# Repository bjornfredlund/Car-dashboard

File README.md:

# Custom ESP32-Based PCB with Bluetooth & Sensor Integration

## Overview

Custom PCB built around the **ESP32** microcontroller. The board integrates multiple sensors and modules, making it suitable for applications such as **data logging, motion tracking, FM transmission, and GNSS-based navigation**. Sample project using the [board](https://github.com/bjornfredlund/ESP32-Car-Dashboard) as a Car dashboard/telemetry unit, providing positiong, velocity, acceleration and bluetooth transmitting capabilities.

## Features
- **ESP32-WROOM-E**
- **TMP117AIDRVR Temperature Sensor**
- **MicroSD Card Reader**
- **TCA9517DGKRQ1 Level shifter for 5v I2C communication** 
- **PCM5102 DAC for Audio Processing**
- **I2C bus to FM Radio Transmitter**
- **LIS2DH12TR Accelerometer**
- **GNSS Receiver via UART**
- **3 User-Programmable Buttons**
## Requirements

- **ESP-IDF v5.3** – Required for firmware development and deployment.

## Applications

- **Wireless Sensor Hub** – Collect and transmit sensor data over Bluetooth.
- **Portable FM Transmitter** – Stream audio to nearby FM receivers.
- **Data Logger** – Store sensor data on an SD card for later analysis.
- **Motion & Position Tracking** – Use accelerometer and GNSS for movement-based applications.

## Getting Started

### 1. **Hardware Setup**

- Power the PCB via **USB or an external battery**.
- Connect necessary peripherals (antennas, audio sources, etc.).

### 2. **Firmware Development**

- Use the **ESP-IDF** or **Arduino IDE** to program the ESP32.
- Implement communication with the sensors and peripherals via **I2C, UART, and SPI**.

### 3. I2C Device addresses 
    TMP117AIDRVR: 0x48
    PCM5102: 0xC0
    LIS2DH12TR: 0x19

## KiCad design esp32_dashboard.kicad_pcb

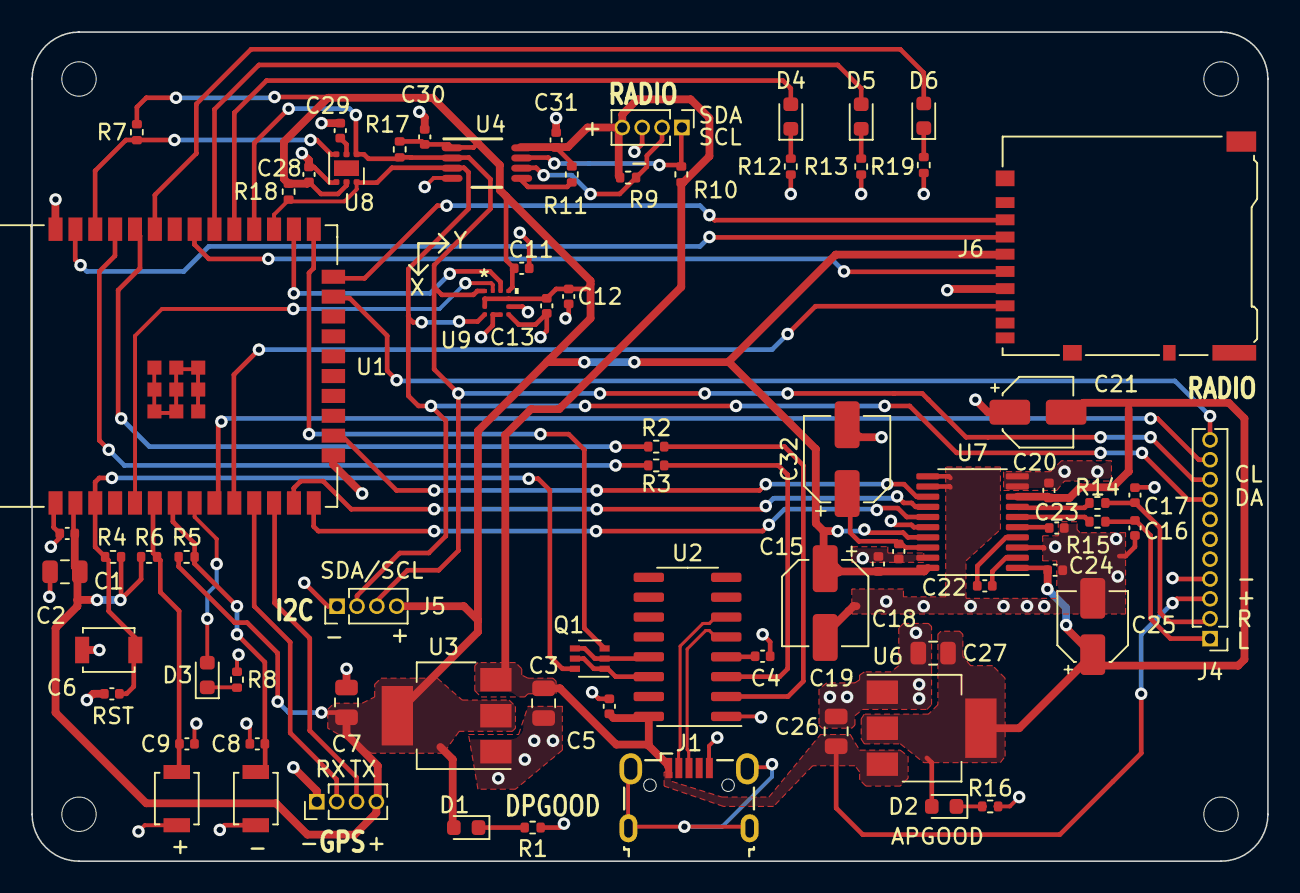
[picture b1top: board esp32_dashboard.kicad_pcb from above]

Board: 2 copper layers, 79.0 x 53.0 mm, 77 parts (0 on the bottom side), 55 nets.

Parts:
C1, C3, C7, C26, C27: 22uF; C_0805_2012Metric
C2, C8, C9, C15, C18, C20, C24: 0.1uF; C_0402_1005Metric
C4, C5, C6, C11, C13, C28, C29, C30, C31: 100nF; C_0402_1005Metric
C12: 10uF; C_0402_1005Metric
C16, C17: 2.2nF; C_0402_1005Metric
C19, C32: 10uF; CP_Elec_5x5.3
C21, C25: 10uF; CP_Elec_4x3
C22, C23: 2.2uF; C_0402_1005Metric
D1, D2, D3, D4, D5, D6: RED; LED_0603_1608Metric
H1, H2, H3, H4: MountingHole; MountingHole_2.2mm_M2
J1: USB_B_Micro; USB_Micro-B_Wuerth_629105150521
J2, J3, J5: Conn_01x04_Pin; PinHeader_1x04_P1.27mm_Vertical
J4: Conn_01x11_Pin; PinHeader_1x11_P1.27mm_Vertical
J6: Micro_SD_Card; microSD_HC_Hirose_DM3AT-SF-PEJM5
Q1: UMH3N; SOT-363_SC-70-6
R1, R8, R12, R13, R16, R19: 1k; R_0402_1005Metric
R2, R3: 0; R_0402_1005Metric
R4, R11: 10k; R_0402_1005Metric
R5, R6: 1K; R_0402_1005Metric
R7, R9, R10, R17, R18: 4k7; R_0402_1005Metric
R14, R15: 470; R_0402_1005Metric
SW1, SW2, SW3: SW_Push; SW_SPST_B3U-1000P
U1: ESP32-WROOM-E; ESP32-WROOM-32E
U2: CH340C; SOIC-16_3.9x9.9mm_P1.27mm
U3, U6: AMS1117-3.3; SOT-223-3_TabPin2
U4: TCA9517DGKRQ1; DGK0008A_N
U7: PCM5102A; TSSOP-20_4.4x6.5mm_P0.65mm
U8: TMP117xxDRV; WSON-6-1EP_2x2mm_P0.65mm_EP1x1.6mm
U9: LIS2DH12TR; LGA-12_STM

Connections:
5V: C3.1, C5.1, C26.1, C31.2, J1.1 (VBUS), J2.4, J4.3, R9.1, R10.1, R11.2, U2.16 (VCC), U3.3 (VI), U4.8 (VCCB), U6.3 (VI)
+3V3: C1.1, C2.1, C7.2, C11.1, C12.1, C13.1, C15.1, C19.1, C28.1, C30.1, D1.2 (A), J3.4, J5.4, J6.4 (VDD), R4.1, R5.1, R6.1, R7.1, R17.1, R18.1, U1.2 (3V3), U3.2 (VO), U4.1 (VCCA), U7.17 (XSMT), U7.20 (DVDD), U8.5 (V+), U9.2 (CS), U9.3 (SDO/SA0), U9.9 (VDD), U9.10 (VDD_IO)
/ACC_INT1: U1.5 (SENSOR_VN/GPIO39/ADC1_CH3), U9.12 (INT1)
/ACC_INT2: U1.26 (ADC2_CH0/GPIO4), U9.11 (INT2)
/Audio/Lout: C16.1, J4.1, R14.2
/Audio/Rout: C17.1, J4.2, R15.1
/BOOT: Q1.3 (C2), U1.25 (GPIO0/BOOT/ADC2_CH1)
/BTN1: C8.1, R5.2, SW1.1, U1.7 (GPIO35/ADC1_CH7)
/BTN2: C9.1, R6.2, SW3.1, U1.6 (GPIO34/ADC1_CH6)
/DTR: Q1.2 (B1), Q1.4 (E2), U2.13 (~DTR)
/EN: C6.1, Q1.6 (C1), R4.2, SW2.1, U1.3 (EN/CHIP_PU)
/RTS: Q1.1 (E1), Q1.5 (B2), U2.14 (~RTS)
/RXD0: R2.2, U1.34 (U0RXD/GPIO3)
/RX_GPS: J3.2, U1.11 (DAC_2/ADC2_CH9/GPIO26)
/SCL5v: J2.1, R10.2, U4.7 (SCLB)
/SDA5v: J2.2, R9.2, U4.6 (SDAB)
/TXD0: R3.2, U1.35 (U0TXD/GPIO1)
/TX_GPS: J3.3, U1.12 (ADC2_CH7/GPIO27)
/T_ALERT: R7.2, U1.36 (GPIO22), U8.3 (ALERT)
/USB+: J1.3 (D+), U2.5 (UD+)
/USB-: J1.2 (D-), U2.6 (UD-)
ESP_OK: D3.2 (A), U1.8 (32K_XP/GPIO32/ADC1_CH4)
GND: C1.2, C2.2, C3.2, C4.1, C5.2, C6.2, C7.1, C8.2, C9.2, C11.2, C12.2, C13.2, C15.2, C16.2, C17.2, C18.1, C19.2, C20.2, C21.1, C23.2, C24.1, C25.2, C26.2, C27.1, C28.2, C29.2, C30.2, C31.1, C32.2, J1.5 (GND), J2.3, J3.1, J4.4, J5.1, J6.6 (VSS), R1.2, R8.2, R12.2, R13.2, R16.2, R19.2, SW1.2, SW2.2, SW3.2, U1.1 (GND), U1.15 (GND), U1.38 (GND), U2.1 (GND), U3.1 (GND), U4.4 (GND), U6.1 (GND), U7.3 (CPGND), U7.9 (AGND), U7.10 (DEMP), U7.11 (FLT), U7.12 (SCK), U7.16 (FMT), U7.19 (DGND), U8.4 (ADD0), U9.5 (RES), U9.6 (GND), U9.7 (GND), U9.8 (GND)
I2S_BCK: U1.16 (MTCK/GPIO13/ADC2_CH4), U7.13 (BCK)
I2S_DATA: U1.13 (MTMS/GPIO14/ADC2_CH6), U7.14 (DIN)
I2S_LRCK: U1.14 (MTDI/GPIO12/ADC2_CH5), U7.15 (LRCK)
LED_0: D4.2 (A), U1.29 (GPIO5)
LED_1: D5.2 (A), U1.30 (GPIO18)
LED_2: D6.2 (A), U1.33 (GPIO21)
MISO: J6.7 (DAT0), U1.10 (DAC_1/ADC2_CH8/GPIO25)
MOSI: J6.3 (CMD), U1.37 (GPIO23)
unnamed: D1.1 (K), R1.1
unnamed: D2.1 (K), R16.1
unnamed: D3.1 (K), R8.1
unnamed: D4.1 (K), R12.1
unnamed: D5.1 (K), R13.1
unnamed: D6.1 (K), R19.1
unnamed: R3.1, U2.3 (RXD)
unnamed: R2.1, U2.2 (TXD)
unnamed: C4.2, U2.4 (V3)
unnamed: R11.1, U4.5 (EN)
unnamed: C22.2, U7.4 (CAPM)
unnamed: C22.1, U7.2 (CAPP)
unnamed: C18.2, C32.1, U7.18 (LDOO)
unnamed: R14.1, U7.6 (OUTL)
unnamed: R15.2, U7.7 (OUTR)
unnamed: C23.1, U7.5 (VNEG)
unnamed: C29.1, U8.2 (GND)
SCK: J6.5 (CLK), U1.31 (GPIO19)
SCL3v3: J4.9, J5.3, R17.2, U1.28 (GPIO17), U4.2 (SCLA), U8.1 (SCL), U9.1 (SCL/SPC)
SDA3v3: J4.8, J5.2, R18.2, U1.27 (GPIO16), U4.3 (SDAA), U8.6 (SDA), U9.4 (SDA/SDI/SDO)
Si Addr: J4.10, U1.9 (32K_XN/GPIO33/ADC1_CH5)
Si RST: J4.11, U1.23 (MTDO/GPIO15/ADC2_CH3)
VDDA: C20.1, C21.2, C24.2, C25.1, C27.2, D2.2 (A), U6.2 (VO), U7.1 (CPVDD), U7.8 (AVDD)
uSD_CS: J6.2 (DAT3/CD), U1.24 (ADC2_CH2/GPIO2)

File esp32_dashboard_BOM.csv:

"Id";"Designator";"Footprint";"Quantity";"Designation";"Manufacturer";"Mfg part";
1;"U9";"LGA-12_STM";1;"LIS2DH12TR";"STMicroelectronics";"LIS2DUX12TR";
2;"C13,C11,C30,C29,C5,C28,C4,C31,C6";"C_0402_1005Metric";9;"100nF";"Murata Electronics";"GMD155R71C104KA11D";
3;"C12";"C_0402_1005Metric";1;"10uF";"KYOCERA AVX";"CM05X5R106M10AH";
4;"C21,C25";"CP_Elec_4x3";2;"10uF";"Wurth Elektronik";"865060643005";
5;"J2,J5,J3";"PinHeader_1x04_P1.27mm_Vertical";3;"Conn_01x04_Pin";"SAMTEC";"SAM1029-04-ND";
6;"D1,D5,D2,D6,D4,D3";"LED_0603_1608Metric";6;"GREEN";"VISHAY";"TLMP1100-GS08";
7;"R10,R9,R7,R18,R17";"R_0402_1005Metric";5;"4k7";"YAGEO";"RC0402JR-074K7L";
8;"R2,R3";"R_0402_1005Metric";2;"0";"Panasonic Electronic Components";"ERJ-2GE0R00X";
9;"U4";"DGK0008A_N";1;"TCA9517DGKRQ1";"Texas Instruments";"TCA9517DGKRQ1";
10;"J4";"PinHeader_1x11_P1.27mm_Vertical";1;"Conn_01x11_Pin";"Adam Tech";"PH1-11-UA";
11;"C24,C20,C2,C15,C8,C9,C18";"C_0402_1005Metric";7;"0.1uF";"TAIYO YUDEN";"MBASU105SB7104KFNA01";
13;"C17,C16";"C_0402_1005Metric";2;"2.2nF";"KEMET";"C0402C222K5RACAUTO";
14;"R11,R4";"R_0402_1005Metric";2;"10k";"VISHAY";"CRCW040210K0FKED";
15;"J1";"USB_Micro-B_Wuerth_629105150521";1;"USB_B_Micro";"Wurth Elektronik";"629105150521";
16;"U7";"TSSOP-20_4.4x6.5mm_P0.65mm";1;"PCM5102A";"Texas Instruments";"PCM5102APWR";
17;"R12,R13,R8,R16,R19,R1";"R_0402_1005Metric";6;"1k";"VISHAY";"CRCW04021K00FKED";
18;"C32,C19";"CP_Elec_5x5.3";2;"10uF";"Nichicon";"UWT1E100MCL1GB";
20;"U8";"WSON-6-1EP_2x2mm_P0.65mm_EP1x1.6mm";1;"TMP117xxDRV";"Texas Instruments";"TMP117AIDRVR";
21;"C1,C7,C27,C3,C26";"C_0805_2012Metric";5;"22uF";"YAGEO";"CC0805MKX5R7BB226";
22;"SW3,SW1,SW2";"SW_SPST_B3U-1000P";3;"SW_Push";"Omron Electronics Inc-EMC Div";"B3U-1000P"
23;"Q1";"SOT-363_SC-70-6";1;"UMH3N";"Jiangsu Changjing Electronics Technology Co., Ltd.";"UMH3N";
24;"R14,R15";"R_0402_1005Metric";2;"470";"VISHAY";"CRCW0402470RFKED";
25;"R6,R5";"R_0402_1005Metric";2;"1K";"VISHAY";"CRCW04021K00FKED.";
26;"U1";"ESP32-WROOM-32E";1;"ESP32-WROOM-E";"Espressif Systems";"ESP32-WROOM-32E-N16";
27;"U2";"SOIC-16_3.9x9.9mm_P1.27mm";1;"CH340C";"WCH(Jiangsu Qin Heng)";"CH340C";
28;"J6";"microSD_HC_Hirose_DM3AT-SF-PEJM5";1;"Micro_SD_Card";"HIROSE;"DM3AT-SF-PEJM5";
29;"U6,U3";"SOT-223-3_TabPin2";2;"AMS1117-3.3";"UMW";"AMS1117-3.3";

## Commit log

2025-03-09 first commit, add readme
2025-03-09 add schematic and pcb
2025-03-09 add kicad project
2025-03-10 add images
2025-03-10 add manufacturing BOM
2025-03-10 Add readme
2025-03-10 update readme, add screenshot
2025-03-10 update with i2c addresses
2025-03-10 update readme with sample project
